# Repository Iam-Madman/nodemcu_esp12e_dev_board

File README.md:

# ESP12E Mains-Powered Breakout Board (v1.0)

A custom, compact development breakout board that integrates a **Hi-Link HLK-10M05** isolated power supply module to power a **NodeMCU (ESP-12E)** directly from household **230V AC mains**.

This board is designed to act as a robust prototyping platform for IoT energy monitoring, automation, and smart infrastructure projects without needing an external DC wall adapter.

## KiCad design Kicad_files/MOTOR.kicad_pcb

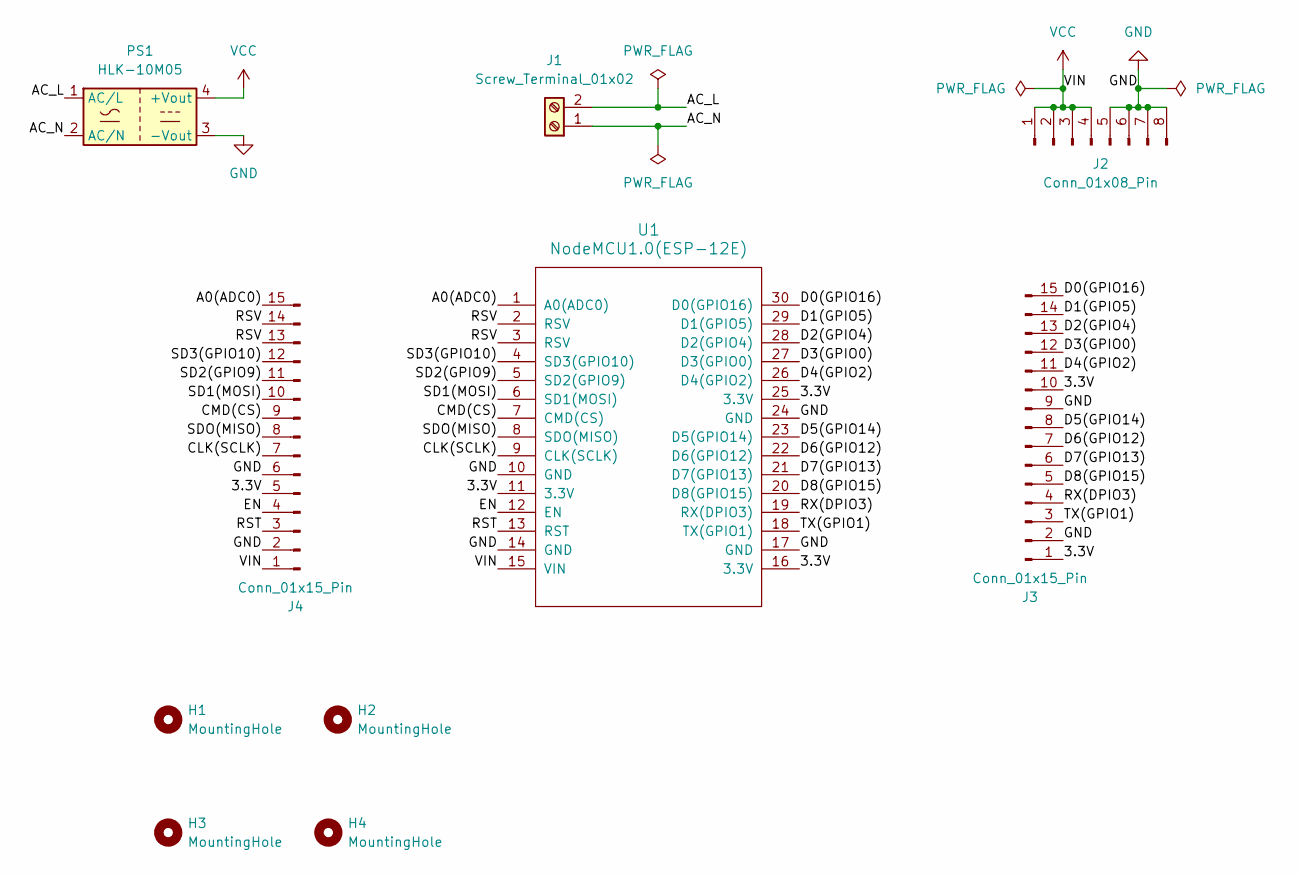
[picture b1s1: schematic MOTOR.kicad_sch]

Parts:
H1, H2, H3, H4: MountingHole; MountingHole_3.2mm_M3
J1: Screw_Terminal_01x02; TerminalBlock_MaiXu_MX126-5.0-02P_1x02_P5.00mm
J2: Conn_01x08_Pin; PinHeader_1x08_P2.54mm_Vertical
J3, J4: Conn_01x15_Pin; PinHeader_1x15_P2.54mm_Vertical
PS1: HLK-10M05; Converter_ACDC_Hi-Link_HLK-10Mxx
U1: NodeMCU1.0(ESP-12E); NodeMCU1.0(12-E)

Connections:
/3.3V: J3.1, J3.10, J4.5, U1.11 (3.3V), U1.16 (3.3V), U1.25 (3.3V)
/A0(ADC0): J4.15, U1.1 (A0(ADC0))
/AC_L: J1.2, PS1.1 (AC/L)
/AC_N: J1.1, PS1.2 (AC/N)
/CLK(SCLK): J4.7, U1.9 (CLK(SCLK))
/CMD(CS): J4.9, U1.7 (CMD(CS))
/D0(GPIO16): J3.15, U1.30 (D0(GPIO16))
/D1(GPIO5): J3.14, U1.29 (D1(GPIO5))
/D2(GPIO4): J3.13, U1.28 (D2(GPIO4))
/D3(GPIO0): J3.12, U1.27 (D3(GPIO0))
/D4(GPIO2): J3.11, U1.26 (D4(GPIO2))
/D5(GPIO14): J3.8, U1.23 (D5(GPIO14))
/D6(GPIO12): J3.7, U1.22 (D6(GPIO12))
/D7(GPIO13): J3.6, U1.21 (D7(GPIO13))
/D8(GPIO15): J3.5, U1.20 (D8(GPIO15))
/EN: J4.4, U1.12 (EN)
/RST: J4.3, U1.13 (RST)
/RSV: J4.13, J4.14, U1.2 (RSV), U1.3 (RSV)
/RX(DPIO3): J3.4, U1.19 (RX(DPIO3))
/SD1(MOSI): J4.10, U1.6 (SD1(MOSI))
/SD2(GPIO9): J4.11, U1.5 (SD2(GPIO9))
/SD3(GPIO10): J4.12, U1.4 (SD3(GPIO10))
/SDO(MISO): J4.8, U1.8 (SDO(MISO))
/TX(GPIO1): J3.3, U1.18 (TX(GPIO1))
GND: J2.5, J2.6, J2.7, J2.8, J3.2, J3.9, J4.2, J4.6, PS1.3 (-Vout), U1.10 (GND), U1.14 (GND), U1.17 (GND), U1.24 (GND)
VCC: J2.1, J2.2, J2.3, J2.4, J4.1, PS1.4 (+Vout), U1.15 (VIN)

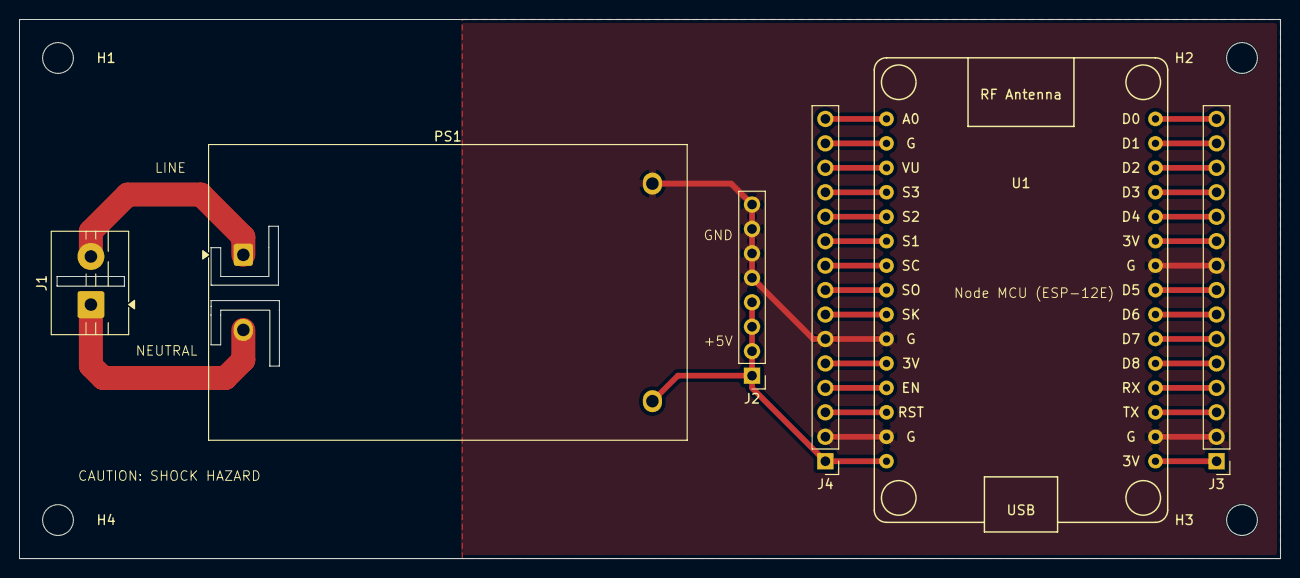
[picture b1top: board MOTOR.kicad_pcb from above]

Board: 2 copper layers, 131.0 x 56.0 mm, 10 parts (0 on the bottom side), 26 nets.

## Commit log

2026-06-06 Initial commit: NodeMCU ESP-12E dev board pcb
2026-06-06 refactor(Changed_dirs): changed_dirs
2026-06-06 feat(generated_fab_files): generated_fab_files
2026-06-06 added 3d images
2026-06-06 renamed image
